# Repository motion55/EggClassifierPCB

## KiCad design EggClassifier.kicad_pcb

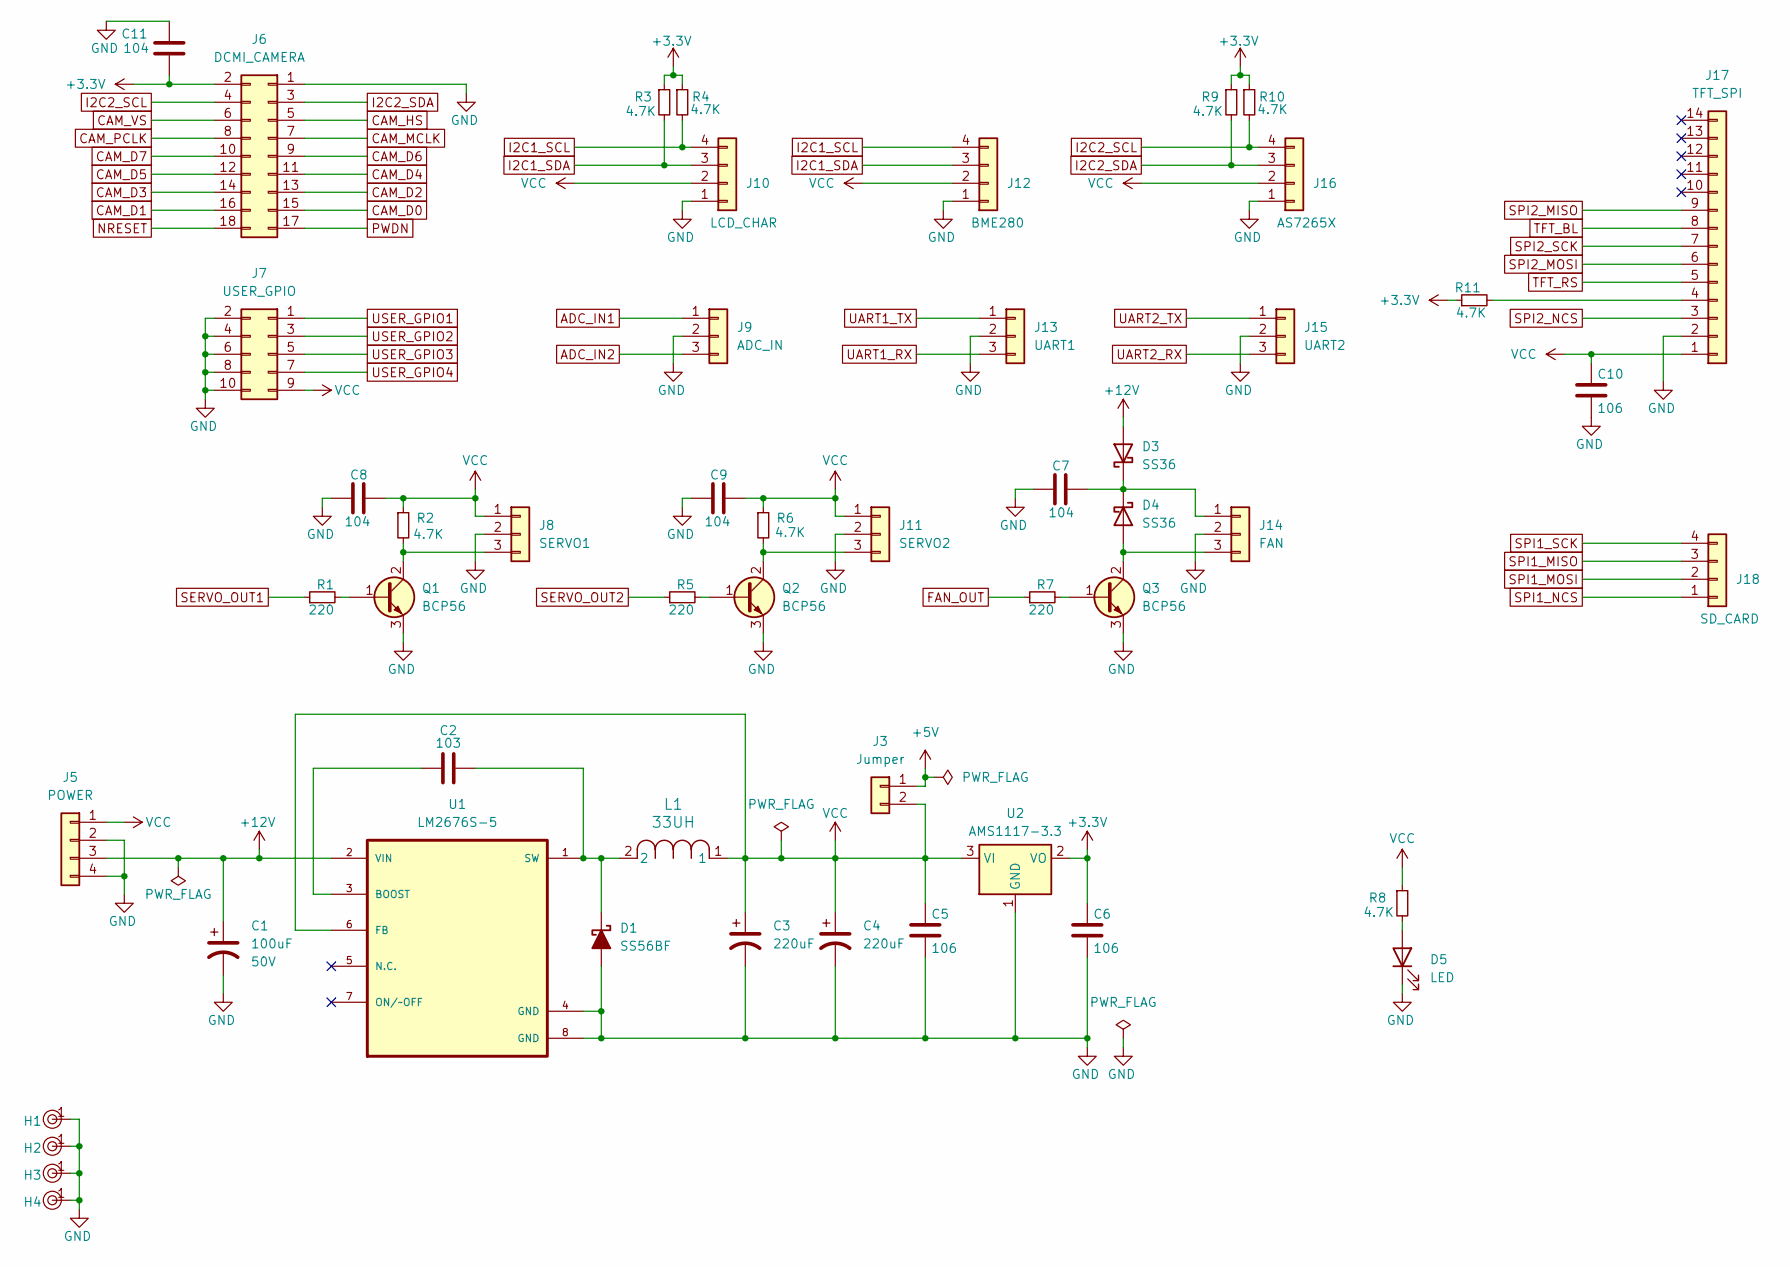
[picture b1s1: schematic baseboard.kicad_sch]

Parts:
C1: 100uF; CP_Radial_D8.0mm_P3.50mm_Hole1.0mm; Tolerance 100%; Voltage 50V
C2: 103; C_0805_2012Metric_Pad1.18x1.45mm_HandSolder
C3, C4: 220uF; CP_Radial_D8.0mm_P3.50mm_Hole1.0mm
C5, C6, C10: 106; C_0805_2012Metric_Pad1.18x1.45mm_HandSolder
C7, C8, C9, C11: 104; C_0805_2012Metric_Pad1.18x1.45mm_HandSolder
D1: SS56BF; D_SMB_Handsoldering
D3, D4: SS36; D_SMA_Handsoldering
D5: LED; LED_0805_2012Metric_Pad1.15x1.40mm_HandSolder
H1, H2, H3, H4: Hole, 3mm
J3: Jumper; PinHeader_1x02_P2.54mm_Vertical
J5: POWER; TerminalBlock_Xinya_XY308-2.54-4P_1x04_P2.54mm_Horizontal
J6: DCMI_CAMERA; PinHeader_2x09_P2.54mm_Vertical
J7: USER_GPIO; PinHeader_2x05_P2.54mm_Vertical
J8: SERVO1; PinHeader_1x03_P2.54mm_Vertical
J9: ADC_IN; PinHeader_1x03_P2.54mm_Vertical
J10: LCD_CHAR; PinHeader_1x04_P2.54mm_Vertical
J11: SERVO2; PinHeader_1x03_P2.54mm_Vertical
J12: BME280; PinHeader_1x04_P2.54mm_Vertical
J13: UART1; PinHeader_1x03_P2.54mm_Vertical
J14: FAN; PinHeader_1x03_P2.54mm_Vertical
J15: UART2; PinHeader_1x03_P2.54mm_Vertical
J16: AS7265X; PinHeader_1x04_P2.54mm_Vertical
J17: TFT_SPI; PinSocket_1x14_P2.54mm_Vertical
J18: SD_CARD; PinSocket_1x04_P2.54mm_Vertical
L1: 33UH; L_SMD,8x8mm
Q1, Q2, Q3: BCP56; SOT-223-3_TabPin2
R1, R5, R7: 220; R_0805_2012Metric_Pad1.20x1.40mm_HandSolder
R2, R3, R4, R6, R8, R9, R10, R11: 4.7K; R_0805_2012Metric_Pad1.20x1.40mm_HandSolder
U1: LM2676S-5; TO127P1435X464-8N
U2: AMS1117-3.3; SOT-223-3_TabPin2

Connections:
+3.3V: C6.1, C11.2, J6.2, R3.1, R4.1, R9.1, R10.1, R11.1, U2.2 (VO); also elsewhere on the board
+5V: J3.1; also elsewhere on the board
+12V: C1.1, D3.2 (A), J5.3, U1.2 (VIN)
ADC_IN1: J9.1; also elsewhere on the board
ADC_IN2: J9.3; also elsewhere on the board
CAM_D0: J6.15; also elsewhere on the board
CAM_D1: J6.16; also elsewhere on the board
CAM_D2: J6.13; also elsewhere on the board
CAM_D3: J6.14; also elsewhere on the board
CAM_D4: J6.11; also elsewhere on the board
CAM_D5: J6.12; also elsewhere on the board
CAM_D6: J6.9; also elsewhere on the board
CAM_D7: J6.10; also elsewhere on the board
CAM_HS: J6.5; also elsewhere on the board
CAM_MCLK: J6.7; also elsewhere on the board
CAM_PCLK: J6.8; also elsewhere on the board
CAM_VS: J6.6; also elsewhere on the board
FAN_OUT: R7.1; also elsewhere on the board
GND: C1.2, C3.2, C4.2, C5.2, C6.2, C7.2, C8.2, C9.2, C10.2, C11.1, D1.2 (A), D5.1 (K), H1.1, H2.1, H3.1, H4.1, J5.2, J5.4, J6.1, J7.2, J7.4, J7.6, J7.8, J7.10, J8.2, J9.2, J10.1, J11.2, J12.1, J13.2, J14.2, J15.2, J16.1, J17.2, Q1.3 (E), Q2.3 (E), Q3.3 (E), U1.4 (GND), U1.8 (GND), U2.1 (GND); also elsewhere on the board
I2C1_SCL: J10.4, J12.4, R4.2; also elsewhere on the board
I2C1_SDA: J10.3, J12.3, R3.2; also elsewhere on the board
I2C2_SCL: J6.4, J16.4, R10.2; also elsewhere on the board
I2C2_SDA: J6.3, J16.3, R9.2; also elsewhere on the board
NRESET: J6.18; also elsewhere on the board
unnamed: C2.2, D1.1 (K), L1.2, U1.1 (SW)
unnamed: C7.1, D3.1 (K), D4.1 (K), J14.1
unnamed: D4.2 (A), J14.3, Q3.2 (C)
unnamed: D5.2 (A), R8.2
unnamed: J8.3, Q1.2 (C), R2.2
unnamed: J11.3, Q2.2 (C), R6.2
unnamed: J17.4, R11.2
unnamed: Q1.1 (B), R1.2
unnamed: Q2.1 (B), R5.2
unnamed: Q3.1 (B), R7.2
unnamed: C2.1, U1.3 (BOOST)
PWDN: J6.17; also elsewhere on the board
SERVO_OUT1: R1.1; also elsewhere on the board
SERVO_OUT2: R5.1; also elsewhere on the board
SPI1_MISO: J18.3; also elsewhere on the board
SPI1_MOSI: J18.2; also elsewhere on the board
SPI1_NCS: J18.1; also elsewhere on the board
SPI1_SCK: J18.4; also elsewhere on the board
SPI2_MISO: J17.9; also elsewhere on the board
SPI2_MOSI: J17.6; also elsewhere on the board
SPI2_NCS: J17.3; also elsewhere on the board
SPI2_SCK: J17.7; also elsewhere on the board
TFT_BL: J17.8; also elsewhere on the board
TFT_RS: J17.5; also elsewhere on the board
UART1_RX: J13.3; also elsewhere on the board
UART1_TX: J13.1; also elsewhere on the board
UART2_RX: J15.3; also elsewhere on the board
UART2_TX: J15.1; also elsewhere on the board
USER_GPIO1: J7.1; also elsewhere on the board
USER_GPIO2: J7.3; also elsewhere on the board
USER_GPIO3: J7.5; also elsewhere on the board
USER_GPIO4: J7.7; also elsewhere on the board
VCC: C3.1, C4.1, C5.1, C8.1, C9.1, C10.1, J3.2, J5.1, J7.9, J8.1, J10.2, J11.1, J12.2, J16.2, J17.1, L1.1, R2.1, R6.1, R8.1, U1.6 (FB), U2.3 (VI)

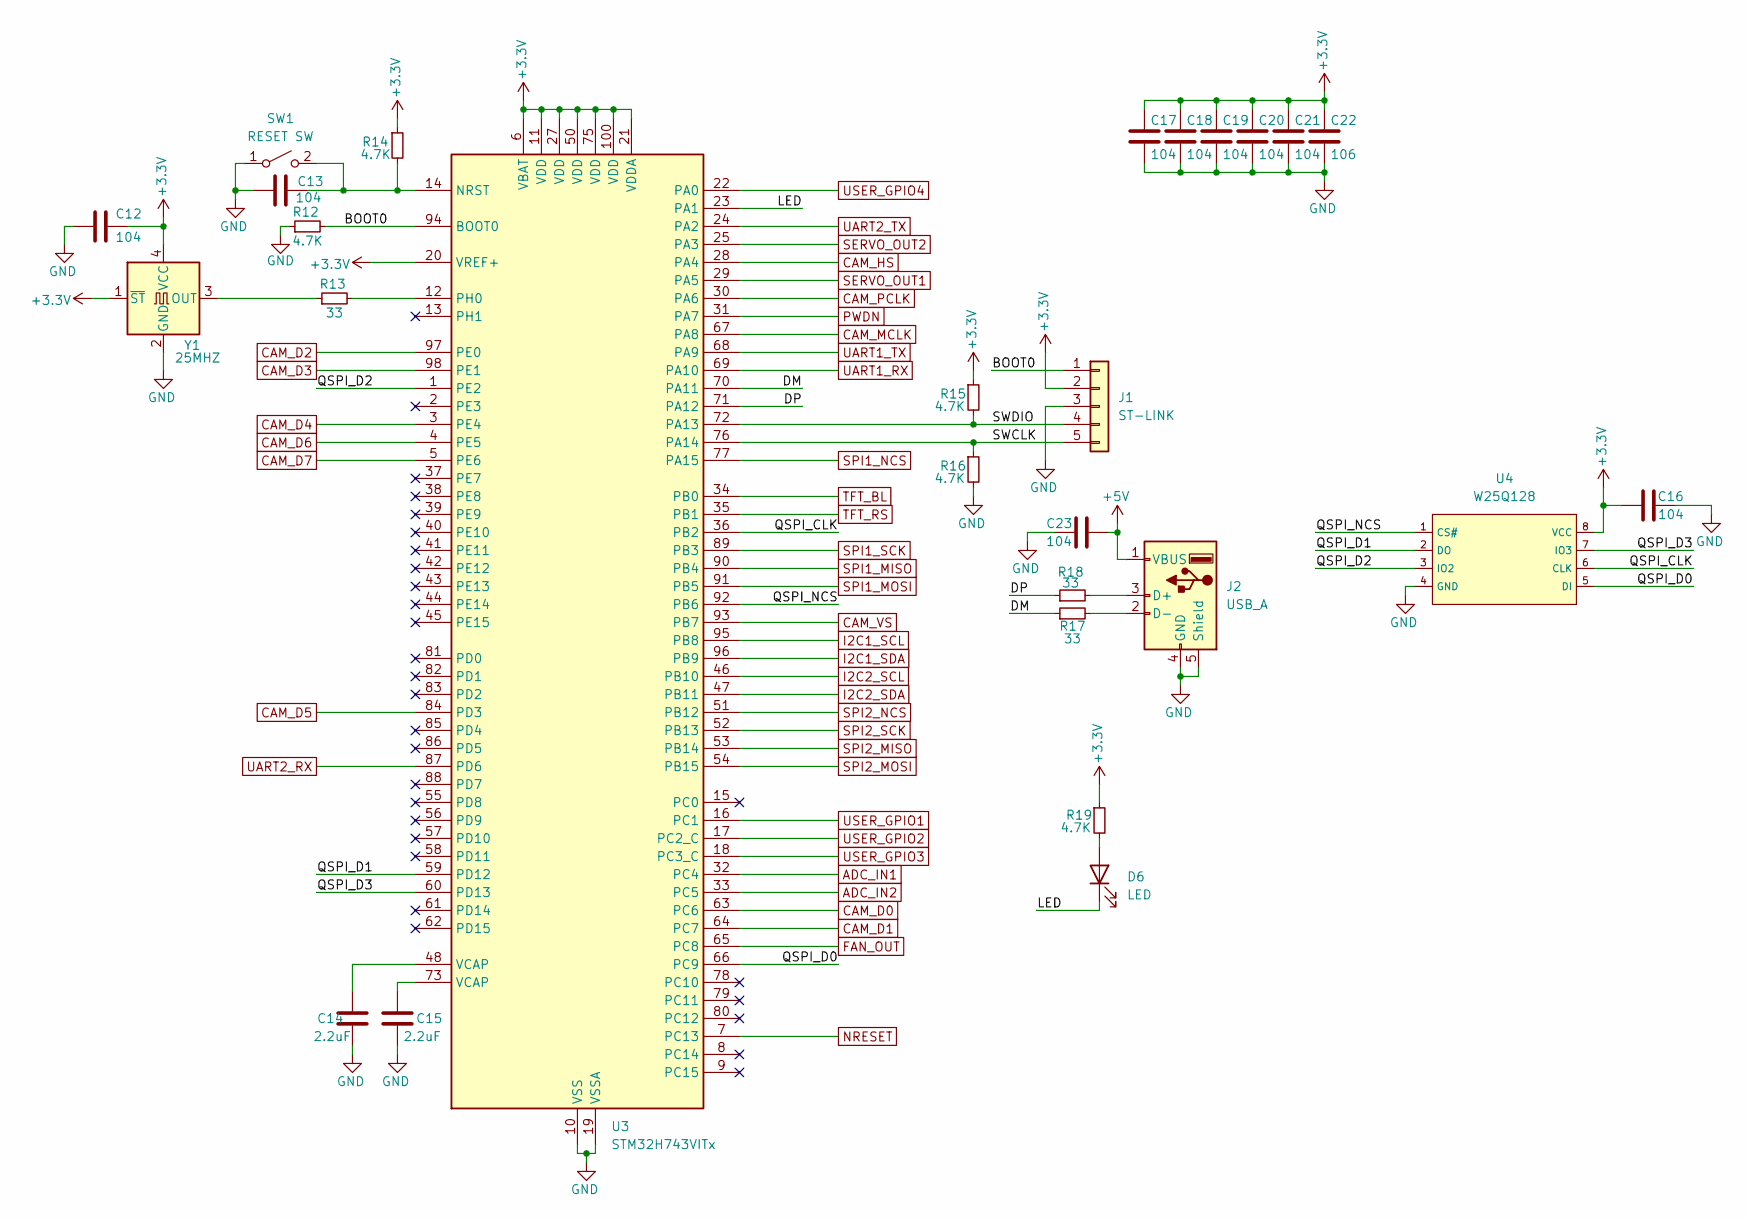
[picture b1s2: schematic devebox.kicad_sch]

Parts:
C12, C13, C16, C17, C18, C19, C20, C21, C23: 104; C_0805_2012Metric_Pad1.18x1.45mm_HandSolder
C14, C15: 2.2uF; C_0805_2012Metric_Pad1.18x1.45mm_HandSolder
C22: 106; C_0805_2012Metric_Pad1.18x1.45mm_HandSolder
D6: LED; LED_0805_2012Metric_Pad1.15x1.40mm_HandSolder
J1: ST-LINK; PinHeader_1x05_P2.54mm_Vertical
J2: USB_A; USB_A_Molex_67643_Horizontal
R12, R14, R15, R16, R19: 4.7K; R_0805_2012Metric_Pad1.20x1.40mm_HandSolder
R13, R17, R18: 33; R_0805_2012Metric_Pad1.20x1.40mm_HandSolder
SW1: RESET SW; SW_PUSH_6mm_H4.3mm
U3: STM32H743VITx; LQFP-100_14x14mm_P0.5mm
U4: W25Q128; SOIC-8_L5.3-W5.3-P1.27-LS8.0-BL; Part W25Q128JVSIQ; LCSC C97521
Y1: 25MHZ; Oscillator_SMD_SeikoEpson_SG8002CA-4Pin_7.0x5.0mm

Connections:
+3.3V: C12.1, C16.1, C17.1, C18.1, C19.1, C20.1, C21.1, C22.1, J1.2, R14.1, R15.1, R19.1, U3.6 (VBAT), U3.11 (VDD), U3.20 (VREF+), U3.21 (VDDA), U3.27 (VDD), U3.50 (VDD), U3.75 (VDD), U3.100 (VDD), U4.8 (VCC), Y1.1 (~ST), Y1.4 (VCC); also elsewhere on the board
+5V: C23.1, J2.1 (VBUS); also elsewhere on the board
/DevEBox/BOOT0: J1.1, R12.2, U3.94 (BOOT0)
/DevEBox/DM: R17.1, U3.70 (PA11)
/DevEBox/DP: R18.1, U3.71 (PA12)
/DevEBox/LED: D6.1 (K), U3.23 (PA1)
/DevEBox/QSPI_CLK: U3.36 (PB2), U4.6 (CLK)
/DevEBox/QSPI_D0: U3.66 (PC9), U4.5 (DI)
/DevEBox/QSPI_D1: U3.59 (PD12), U4.2 (DO)
/DevEBox/QSPI_D2: U3.1 (PE2), U4.3 (IO2)
/DevEBox/QSPI_D3: U3.60 (PD13), U4.7 (IO3)
/DevEBox/QSPI_NCS: U3.92 (PB6), U4.1 (CS#)
/DevEBox/SWCLK: J1.5, R16.1, U3.76 (PA14)
/DevEBox/SWDIO: J1.4, R15.2, U3.72 (PA13)
ADC_IN1: U3.32 (PC4); also elsewhere on the board
ADC_IN2: U3.33 (PC5); also elsewhere on the board
CAM_D0: U3.63 (PC6); also elsewhere on the board
CAM_D1: U3.64 (PC7); also elsewhere on the board
CAM_D2: U3.97 (PE0); also elsewhere on the board
CAM_D3: U3.98 (PE1); also elsewhere on the board
CAM_D4: U3.3 (PE4); also elsewhere on the board
CAM_D5: U3.84 (PD3); also elsewhere on the board
CAM_D6: U3.4 (PE5); also elsewhere on the board
CAM_D7: U3.5 (PE6); also elsewhere on the board
CAM_HS: U3.28 (PA4); also elsewhere on the board
CAM_MCLK: U3.67 (PA8); also elsewhere on the board
CAM_PCLK: U3.30 (PA6); also elsewhere on the board
CAM_VS: U3.93 (PB7); also elsewhere on the board
FAN_OUT: U3.65 (PC8); also elsewhere on the board
GND: C12.2, C13.2, C14.2, C15.2, C16.2, C17.2, C18.2, C19.2, C20.2, C21.2, C22.2, C23.2, J1.3, J2.4 (GND), J2.5 (Shield), R12.1, R16.2, SW1.1 (A), U3.10 (VSS), U3.19 (VSSA), U3.26 (VSS), U3.49 (VSS), U3.74 (VSS), U3.99 (VSS), U4.4 (GND), Y1.2 (GND); also elsewhere on the board
I2C1_SCL: U3.95 (PB8); also elsewhere on the board
I2C1_SDA: U3.96 (PB9); also elsewhere on the board
I2C2_SCL: U3.46 (PB10); also elsewhere on the board
I2C2_SDA: U3.47 (PB11); also elsewhere on the board
NRESET: U3.7 (PC13); also elsewhere on the board
unnamed: C14.1, U3.48 (VCAP)
unnamed: C15.1, U3.73 (VCAP)
unnamed: D6.2 (A), R19.2
unnamed: J2.3 (D+), R18.2
unnamed: J2.2 (D-), R17.2
unnamed: C13.1, R14.2, SW1.2 (B), U3.14 (NRST)
unnamed: R13.2, U3.12 (PH0)
unnamed: R13.1, Y1.3 (OUT)
PWDN: U3.31 (PA7); also elsewhere on the board
SERVO_OUT1: U3.29 (PA5); also elsewhere on the board
SERVO_OUT2: U3.25 (PA3); also elsewhere on the board
SPI1_MISO: U3.90 (PB4); also elsewhere on the board
SPI1_MOSI: U3.91 (PB5); also elsewhere on the board
SPI1_NCS: U3.77 (PA15); also elsewhere on the board
SPI1_SCK: U3.89 (PB3); also elsewhere on the board
SPI2_MISO: U3.53 (PB14); also elsewhere on the board
SPI2_MOSI: U3.54 (PB15); also elsewhere on the board
SPI2_NCS: U3.51 (PB12); also elsewhere on the board
SPI2_SCK: U3.52 (PB13); also elsewhere on the board
TFT_BL: U3.34 (PB0); also elsewhere on the board
TFT_RS: U3.35 (PB1); also elsewhere on the board
UART1_RX: U3.69 (PA10); also elsewhere on the board
UART1_TX: U3.68 (PA9); also elsewhere on the board
UART2_RX: U3.87 (PD6); also elsewhere on the board
UART2_TX: U3.24 (PA2); also elsewhere on the board
USER_GPIO1: U3.16 (PC1); also elsewhere on the board
USER_GPIO2: U3.17 (PC2_C); also elsewhere on the board
USER_GPIO3: U3.18 (PC3_C); also elsewhere on the board
USER_GPIO4: U3.22 (PA0); also elsewhere on the board

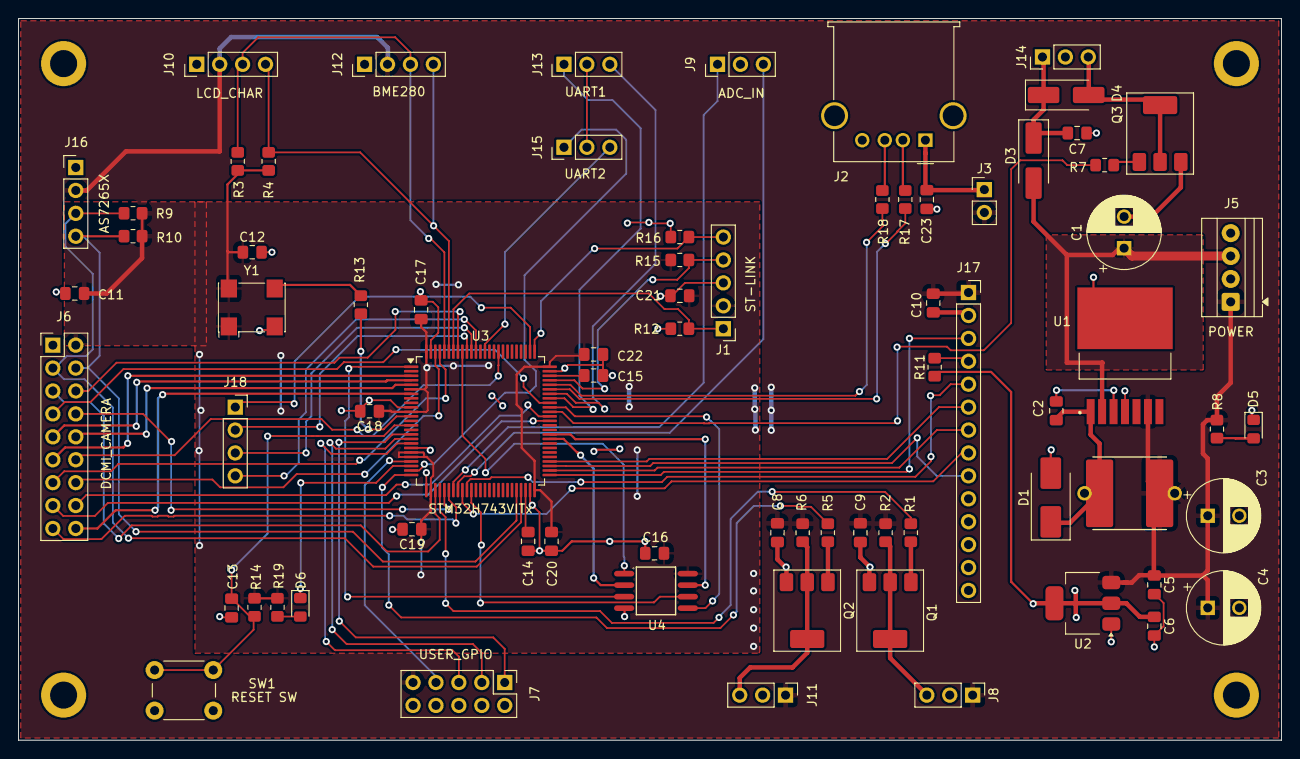
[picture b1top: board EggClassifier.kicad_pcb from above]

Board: 2 copper layers, 140.0 x 80.0 mm, 78 parts (0 on the bottom side), 77 nets.

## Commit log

2025-03-29 initial
2025-03-30 snapshot prior to clearing PCB
2025-03-30 completed part placement
2025-03-30 end of day snapshot
2025-03-31 pass DRC without error
2025-03-31 Discovered no SPI2 on checking
2025-04-01 art work finished but DCMI camera needs to be resolved
2025-04-01 change dcmi connector and pass DRC. TFT SPI used SPI1
2025-04-01 Update PDF schematics
2025-04-01 fix missing SPI2 on TFT_SPI
2025-04-01 semi final PCN layout
2025-04-02 pass completed layout and pass DRC
2025-04-02 snapshot
2025-04-02 resize electrolytic capacitors hole size to be the same as the connector pins.
2025-04-03 change capacitor footprint
2025-04-03 Ordered from JLPCB
2025-04-03 start of new board with STM32H743VIT6 included
2025-04-14 adjust schematic and PCB to reflect as build condition
2025-04-14 archive symbols to local Library.kicad_sym
2025-04-14 snapshot prior to merge
2025-04-19 moved connectors
2025-04-19 Add footprints to project library
2025-04-20 sync from JLCPCB
2025-04-20 sync from JLCPCB mcuheaders.kicad_sch
2025-04-20 update footprints
2025-04-21 snapshot prior to simplify
2025-04-21 almost finsihed
2025-04-22 complete PCB layout
2025-04-22 more fine tuning
2025-04-23 yet more tweaks
2025-04-24 final version before change in PCB dimensions
2025-04-24 change board to dimensions 120mm x 80mm
2025-04-25 finished layout;. H743 with SD-Card
2025-04-26 final version of 80mmx140mm PCB
2025-04-26 Snapshot prior to making JLC version
